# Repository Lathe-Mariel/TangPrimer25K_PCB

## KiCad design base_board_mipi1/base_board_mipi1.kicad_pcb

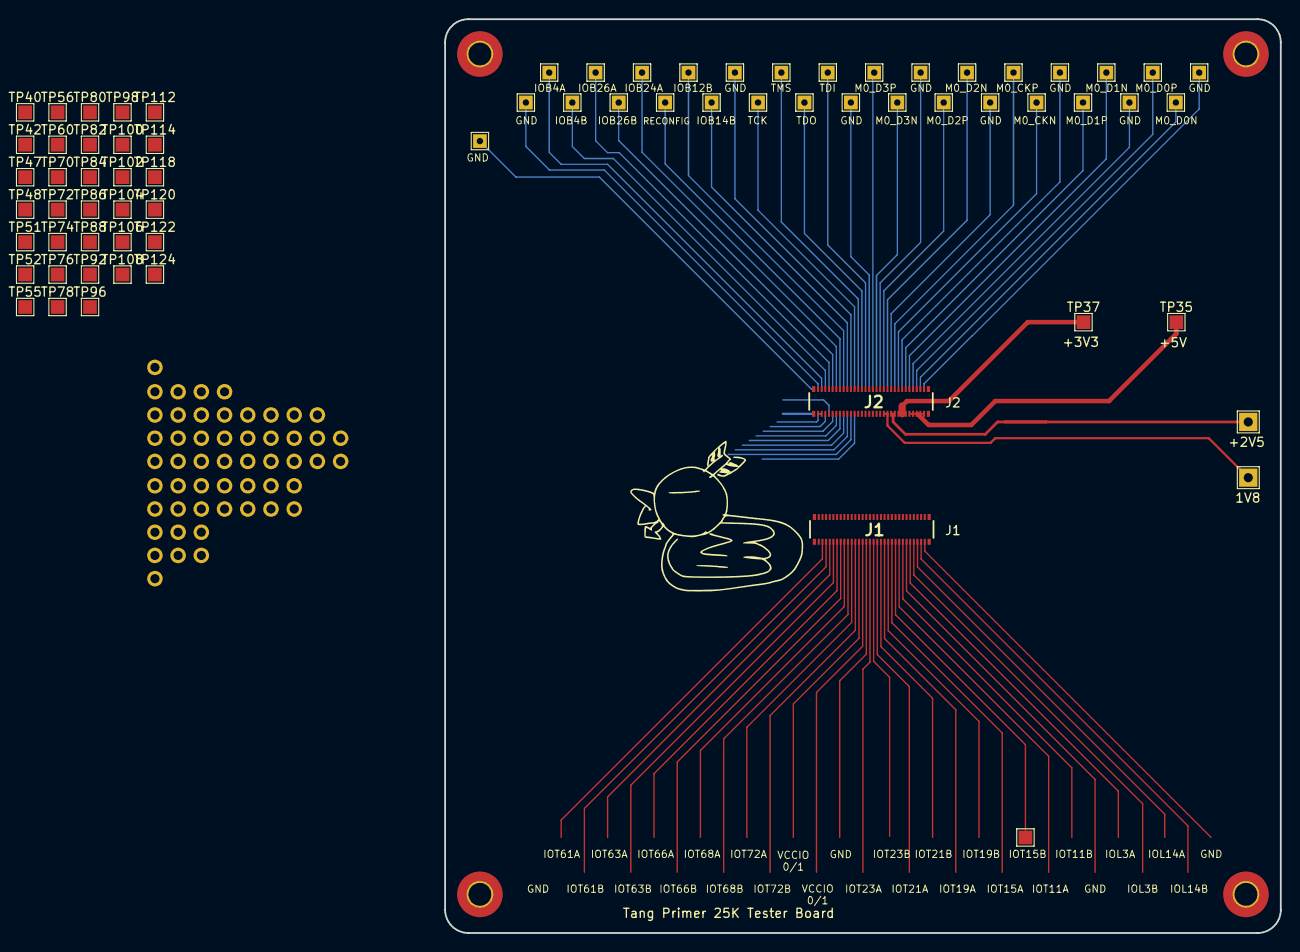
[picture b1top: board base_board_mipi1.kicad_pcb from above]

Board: 2 copper layers, 91.4 x 100.0 mm, 69 parts (0 on the bottom side), 55 nets.

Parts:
J1, J2: DF40C-60DP-0.4V_51_; DF40C-60DS-0.4V_51_
TP1, TP2, TP3, TP4, TP5, TP6, TP7, TP8, TP9, TP10, TP11, TP12, TP13, TP14, TP15, TP16, TP17, TP18, TP19, TP20, TP21, TP22, TP23, TP24, TP25, TP26, TP27, TP28, TP29, TP30, TP61: TestPoint; TestPoint_THTPad_1.5x1.5mm_Drill0.7mm
TP35, TP37, TP40, TP42, TP47, TP48, TP51, TP52, TP55, TP56, TP60, TP70, TP72, TP74, TP76, TP78, TP80, TP82, TP84, TP86, TP88, TP92, TP96, TP98, TP100, TP102, TP104, TP106, TP108, TP110, TP112, TP114, TP118, TP120, TP122, TP124: TestPoint; TestPoint_Pad_1.5x1.5mm

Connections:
+2V5: J2.42, J2.44, TP40.1
+3V3: J2.46, J2.48, J2.50, TP37.1
+5V: J2.52, J2.54, J2.56, J2.58, J2.60, TP35.1
/IOB26A: J2.7, TP27.1
/IOB26B: J2.9, TP26.1
/IOL3A: J1.52, TP118.1
/IOL3B: J1.54, TP120.1
/IOL14A: J1.56, TP122.1
/IOL14B: J1.58, TP124.1
/IOR20A: J2.10, TP56.1
/IOR20B: J2.12, TP55.1
/IOR24A: J2.18, TP52.1
/IOR24B: J2.20, TP51.1
/IOR33A: J2.26, TP48.1
/IOR33B: J2.28, TP47.1
/IOT11A: J1.46, TP112.1
/IOT11B: J1.48, TP114.1
/IOT15A: J1.42, TP108.1
/IOT15B: J1.44, TP110.1
/IOT19A: J1.38, TP104.1
/IOT19B: J1.40, TP106.1
/IOT21A: J1.34, TP100.1
/IOT21B: J1.36, TP102.1
/IOT23A: J1.30, TP96.1
/IOT23B: J1.32, TP98.1
/IOT61A: J1.4, TP70.1
/IOT61B: J1.6, TP72.1
/IOT63A: J1.8, TP74.1
/IOT63B: J1.10, TP76.1
/IOT66A: J1.12, TP78.1
/IOT66B: J1.14, TP80.1
/IOT68A: J1.16, TP82.1
/IOT68B: J1.18, TP84.1
/IOT72A: J1.20, TP86.1
/IOT72B: J1.22, TP88.1
/M0_CKN: J2.45, TP8.1
/M0_CKP: J2.43, TP9.1
/M0_D0N: J2.57, TP2.1
/M0_D0P: J2.55, TP3.1
/M0_D1N: J2.51, TP5.1
/M0_D1P: J2.49, TP6.1
/M0_D2N: J2.39, TP11.1
/M0_D2P: J2.37, TP12.1
/M0_D3N: J2.33, TP14.1
/M0_D3P: J2.31, TP15.1
/RECONFIG: J2.13, TP24.1
/TCK: J2.21, TP20.1
/TDI: J2.27, TP17.1
/TDO: J2.25, TP18.1
/TMS: J2.23, TP19.1
/VCCIO0/1: J1.24, J1.26, TP92.1
/VCCIO2/3: J2.2, J2.4, TP60.1
/VCCIO6/7: J1.29, J1.31
/VDD_1V8: J2.38, J2.40, TP42.1
GND: J1.1, J1.2, J1.15, J1.27, J1.28, J1.45, J1.50, J1.59, J1.60, J1.61, J1.62, J1.63, J1.64, J2.1, J2.19, J2.29, J2.35, J2.41, J2.47, J2.53, J2.59, J2.61, J2.62, J2.63, J2.64, TP1.1, TP4.1, TP7.1, TP10.1, TP13.1, TP16.1, TP21.1, TP30.1, TP61.1

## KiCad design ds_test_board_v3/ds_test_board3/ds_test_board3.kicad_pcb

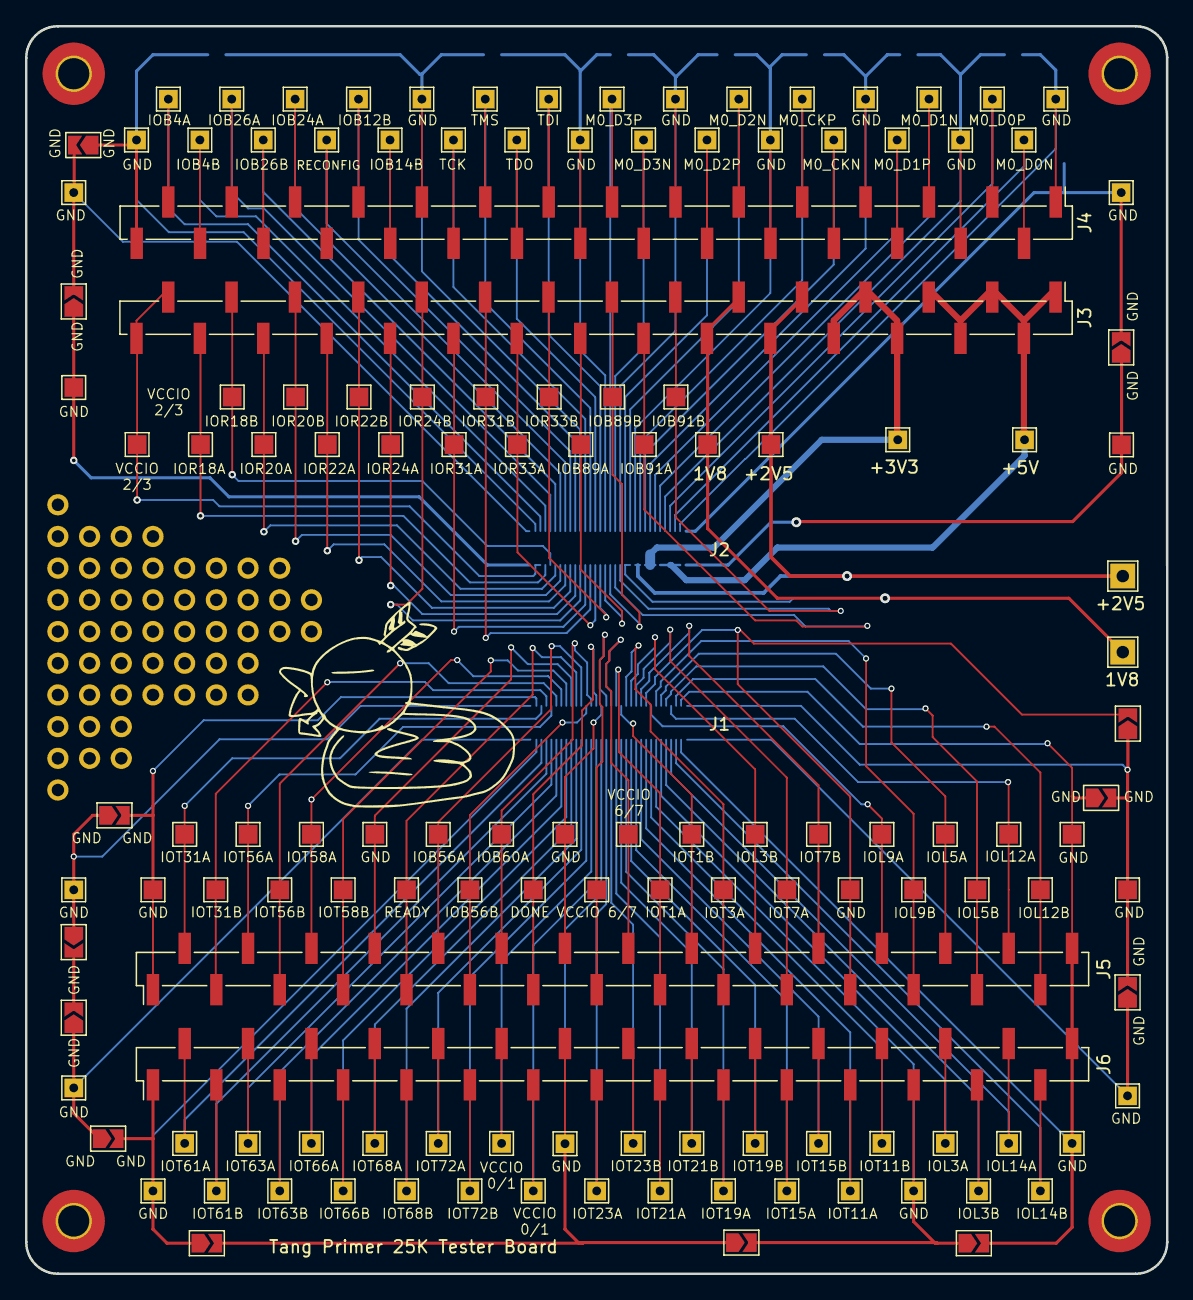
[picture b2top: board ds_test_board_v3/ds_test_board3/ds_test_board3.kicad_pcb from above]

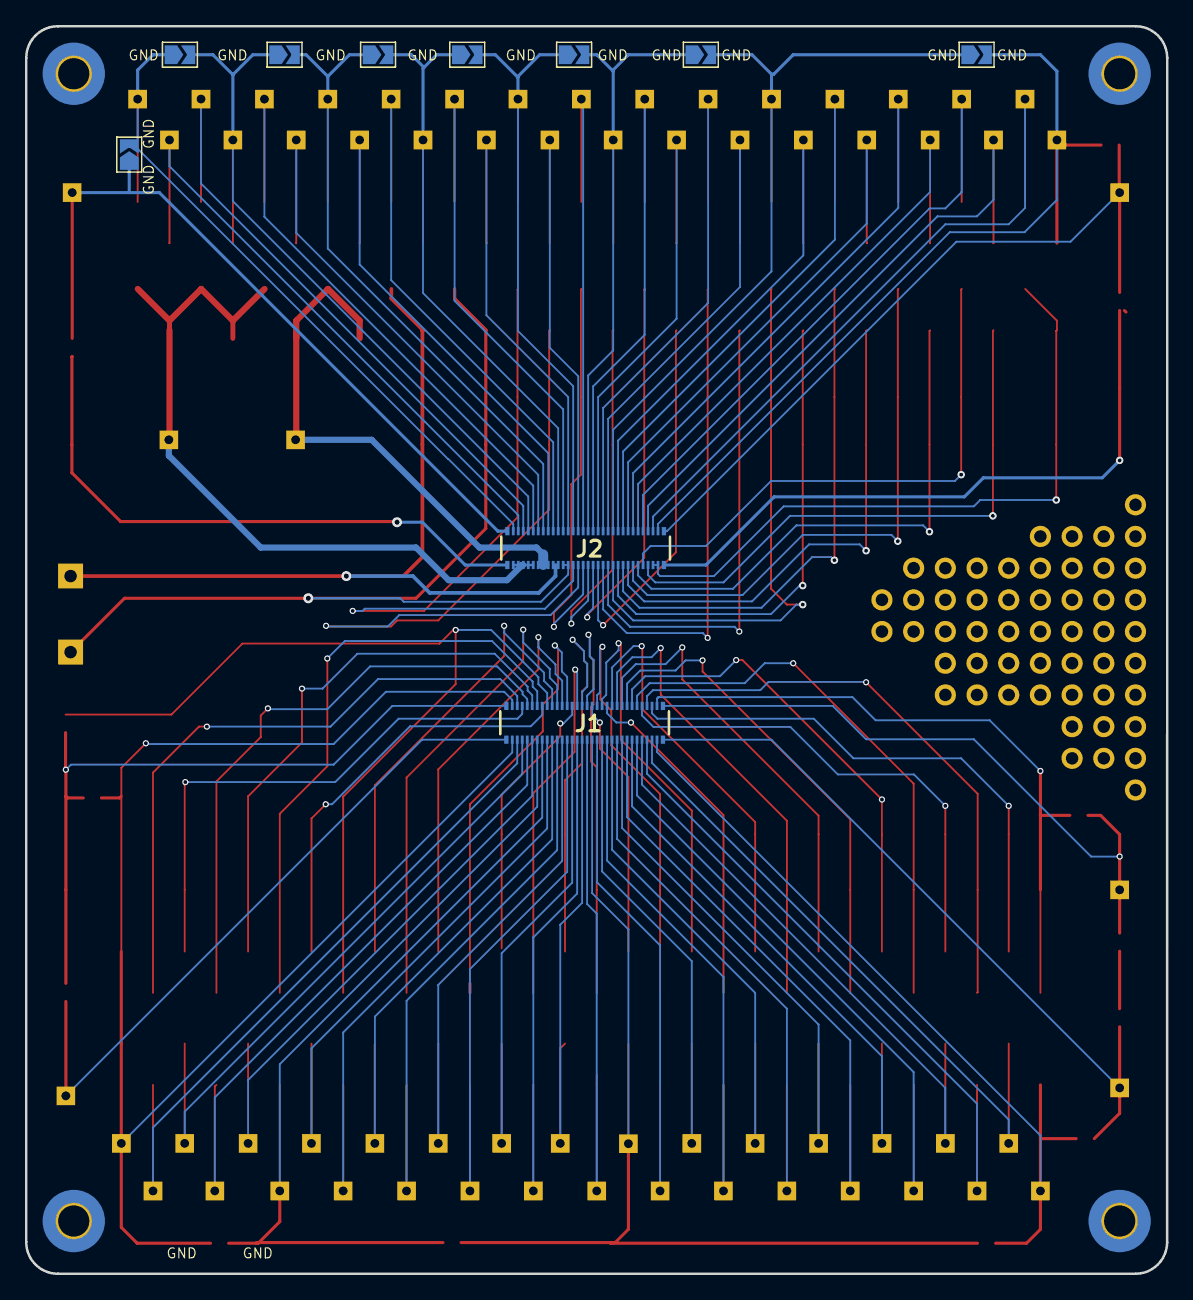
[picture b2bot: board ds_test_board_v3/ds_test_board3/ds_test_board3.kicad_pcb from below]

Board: 2 copper layers, 91.4 x 100.0 mm, 125 parts (2 on the bottom side), 97 nets.

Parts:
J1, J2: DF40C-60DP-0.4V_51_
J3, J4, J5, J6: Conn_01x30; PinHeader_1x30_P2.54mm_Vertical_SMD_Pin1Left
TP1, TP2, TP3, TP4, TP5, TP6, TP7, TP8, TP9, TP10, TP11, TP12, TP13, TP14, TP15, TP16, TP17, TP18, TP19, TP20, TP21, TP22, TP23, TP24, TP25, TP26, TP27, TP28, TP29, TP30, TP35, TP37, TP61, TP63, TP66, TP67, TP69, TP71, TP73, TP75, TP77, TP79, TP81, TP83, TP85, TP87, TP89, TP91, TP93, TP93#2, TP95, TP95#2, TP101, TP103, TP105, TP107, TP109, TP111, TP113, TP115, TP117, TP119, TP121, TP123, TP125, TP127, TP128: TestPoint; TestPoint_THTPad_1.5x1.5mm_Drill0.7mm
TP40, TP42, TP43, TP44, TP45, TP46, TP47, TP48, TP49, TP50, TP51, TP52, TP53, TP54, TP55, TP56, TP57, TP58, TP60, TP62, TP64, TP65, TP68, TP70, TP72, TP74, TP76, TP78, TP80, TP82, TP84, TP86, TP88, TP92, TP94, TP94#2, TP96, TP98, TP100, TP102, TP104, TP106, TP108, TP110, TP112, TP114, TP116, TP118, TP120, TP122, TP124, TP126: TestPoint; TestPoint_Pad_1.5x1.5mm

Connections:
+2V5: J2.42, J2.44, J3.9, J3.10, TP40.1
+3V3: J2.46, J2.48, J2.50, J3.6, J3.7, J3.8, TP37.1
+5V: J2.52, J2.54, J2.56, J2.58, J2.60, J3.1, J3.2, J3.3, J3.4, J3.5, TP35.1
/DONE: J1.25, J5.13, TP102.1
/IOB4A: J2.3, J4.29, TP29.1
/IOB4B: J2.5, J4.28, TP28.1
/IOB12B: J2.15, J4.23, TP23.1
/IOB14B: J2.17, J4.22, TP22.1
/IOB24A: J2.11, J4.25, TP25.1
/IOB26A: J2.7, J4.27, TP27.1
/IOB26B: J2.9, J4.26, TP26.1
/IOB56A: J1.19, J5.10, TP108.1
/IOB56B: J1.21, J5.11, TP106.1
/IOB60A: J1.23, J5.12, TP104.1
/IOB89A: J2.30, J3.16, TP46.1
/IOB89B: J2.32, J3.15, TP45.1
/IOB91A: J2.34, J3.14, TP44.1
/IOB91B: J2.36, J3.13, TP43.1
/IOL3A: J1.52, J6.26, TP75.1
/IOL3B: J1.54, J6.27, TP73.1
/IOL5A: J1.51, J5.26, TP76.1
/IOL5B: J1.53, J5.27, TP74.1
/IOL9A: J1.47, J5.24, TP80.1
/IOL9B: J1.49, J5.25, TP78.1
/IOL12A: J1.55, J5.28, TP72.1
/IOL12B: J1.57, J5.29, TP70.1
/IOL14A: J1.56, J6.28, TP71.1
/IOL14B: J1.58, J6.29, TP69.1
/IOR18A: J2.6, J3.28, TP58.1
/IOR18B: J2.8, J3.27, TP57.1
/IOR20A: J2.10, J3.26, TP56.1
/IOR20B: J2.12, J3.25, TP55.1
/IOR22A: J2.14, J3.24, TP54.1
/IOR22B: J2.16, J3.23, TP53.1
/IOR24A: J2.18, J3.22, TP52.1
/IOR24B: J2.20, J3.21, TP51.1
/IOR31A: J2.22, J3.20, TP50.1
/IOR31B: J2.24, J3.19, TP49.1
/IOR33A: J2.26, J3.18, TP48.1
/IOR33B: J2.28, J3.17, TP47.1
/IOT1A: J1.33, J5.17, TP94#2.1
/IOT1B: J1.35, J5.18, TP94.1
/IOT3A: J1.37, J5.19, TP92.1
/IOT3B: J1.39, J5.20, TP88.1
/IOT7A: J1.41, J5.21, TP86.1
/IOT7B: J1.43, J5.22, TP84.1
/IOT11A: J1.46, J6.23, TP81.1
/IOT11B: J1.48, J6.24, TP79.1
/IOT15A: J1.42, J6.21, TP85.1
/IOT15B: J1.44, J6.22, TP83.1
/IOT19A: J1.38, J6.19, TP89.1
/IOT19B: J1.40, J6.20, TP87.1
/IOT21A: J1.34, J6.17, TP93.1
/IOT21B: J1.36, J6.18, TP91.1
/IOT23A: J1.30, J6.15, TP95.1
/IOT23B: J1.32, J6.16, TP93#2.1
/IOT58A: J1.11, J5.6, TP116.1
/IOT58B: J1.13, J5.7, TP114.1
/IOT61A: J1.4, J6.2, TP123.1
/IOT61B: J1.6, J6.3, TP121.1
/IOT63A: J1.8, J6.4, TP119.1
/IOT63B: J1.10, J6.5, TP117.1
/IOT66A: J1.12, J6.6, TP115.1
/IOT66B: J1.14, J6.7, TP113.1
/IOT68A: J1.16, J6.8, TP111.1
/IOT68B: J1.18, J6.9, TP109.1
/IOT72A: J1.20, J6.10, TP107.1
/IOT72B: J1.22, J6.11, TP105.1
/M0_CKN: J2.45, J4.8, TP8.1
/M0_CKP: J2.43, J4.9, TP9.1
/M0_D0N: J2.57, J4.2, TP2.1
/M0_D0P: J2.55, J4.3, TP3.1
/M0_D1N: J2.51, J4.5, TP5.1
/M0_D1P: J2.49, J4.6, TP6.1
/M0_D2N: J2.39, J4.11, TP11.1
/M0_D2P: J2.37, J4.12, TP12.1
/M0_D3N: J2.33, J4.14, TP14.1
/M0_D3P: J2.31, J4.15, TP15.1
/READY: J1.17, J5.9, TP110.1
/RECONFIG: J2.13, J4.24, TP24.1
/TCK: J2.21, J4.20, TP20.1
/TDI: J2.27, J4.17, TP17.1
/TDO: J2.25, J4.18, TP18.1
/TMS: J2.23, J4.19, TP19.1
/VCCIO0/1: J1.24, J1.26, J6.12, J6.13, TP101.1, TP103.1
/VCCIO2/3: J2.2, J2.4, J3.29, J3.30, TP60.1
/VCCIO6/7: J1.29, J1.31, J5.15, J5.16, TP96.1, TP98.1
/VDD_1V8: J2.38, J2.40, J3.11, J3.12, TP42.1
GND: J1.1, J1.2, J1.15, J1.27, J1.28, J1.45, J1.50, J1.59, J1.60, J2.1, J2.19, J2.29, J2.35, J2.41, J2.47, J2.53, J2.59, J2.61, J2.62, J2.63, J2.64, J4.1, J4.4, J4.7, J4.10, J4.13, J4.16, J4.21, J4.30, J5.1, J5.8, J5.14, J5.23, J5.30, J6.1, J6.14, J6.25, J6.30, TP1.1, TP4.1, TP7.1, TP10.1, TP13.1, TP16.1, TP21.1, TP30.1, TP61.1, TP62.1, TP63.1, TP64.1, TP67.1, TP68.1, TP77.1, TP82.1, TP95#2.1, TP100.1, TP112.1, TP125.1, TP126.1
IOT31A: J1.3, J5.2, TP124.1
IOT31B: J1.5, J5.3, TP122.1
IOT56A: J1.7, J5.4, TP120.1
IOT56B: J1.9, J5.5, TP118.1
unnamed: J1.61, TP128.1
unnamed: J1.62, TP127.1
unnamed: J1.63, TP65.1
unnamed: J1.64, TP66.1

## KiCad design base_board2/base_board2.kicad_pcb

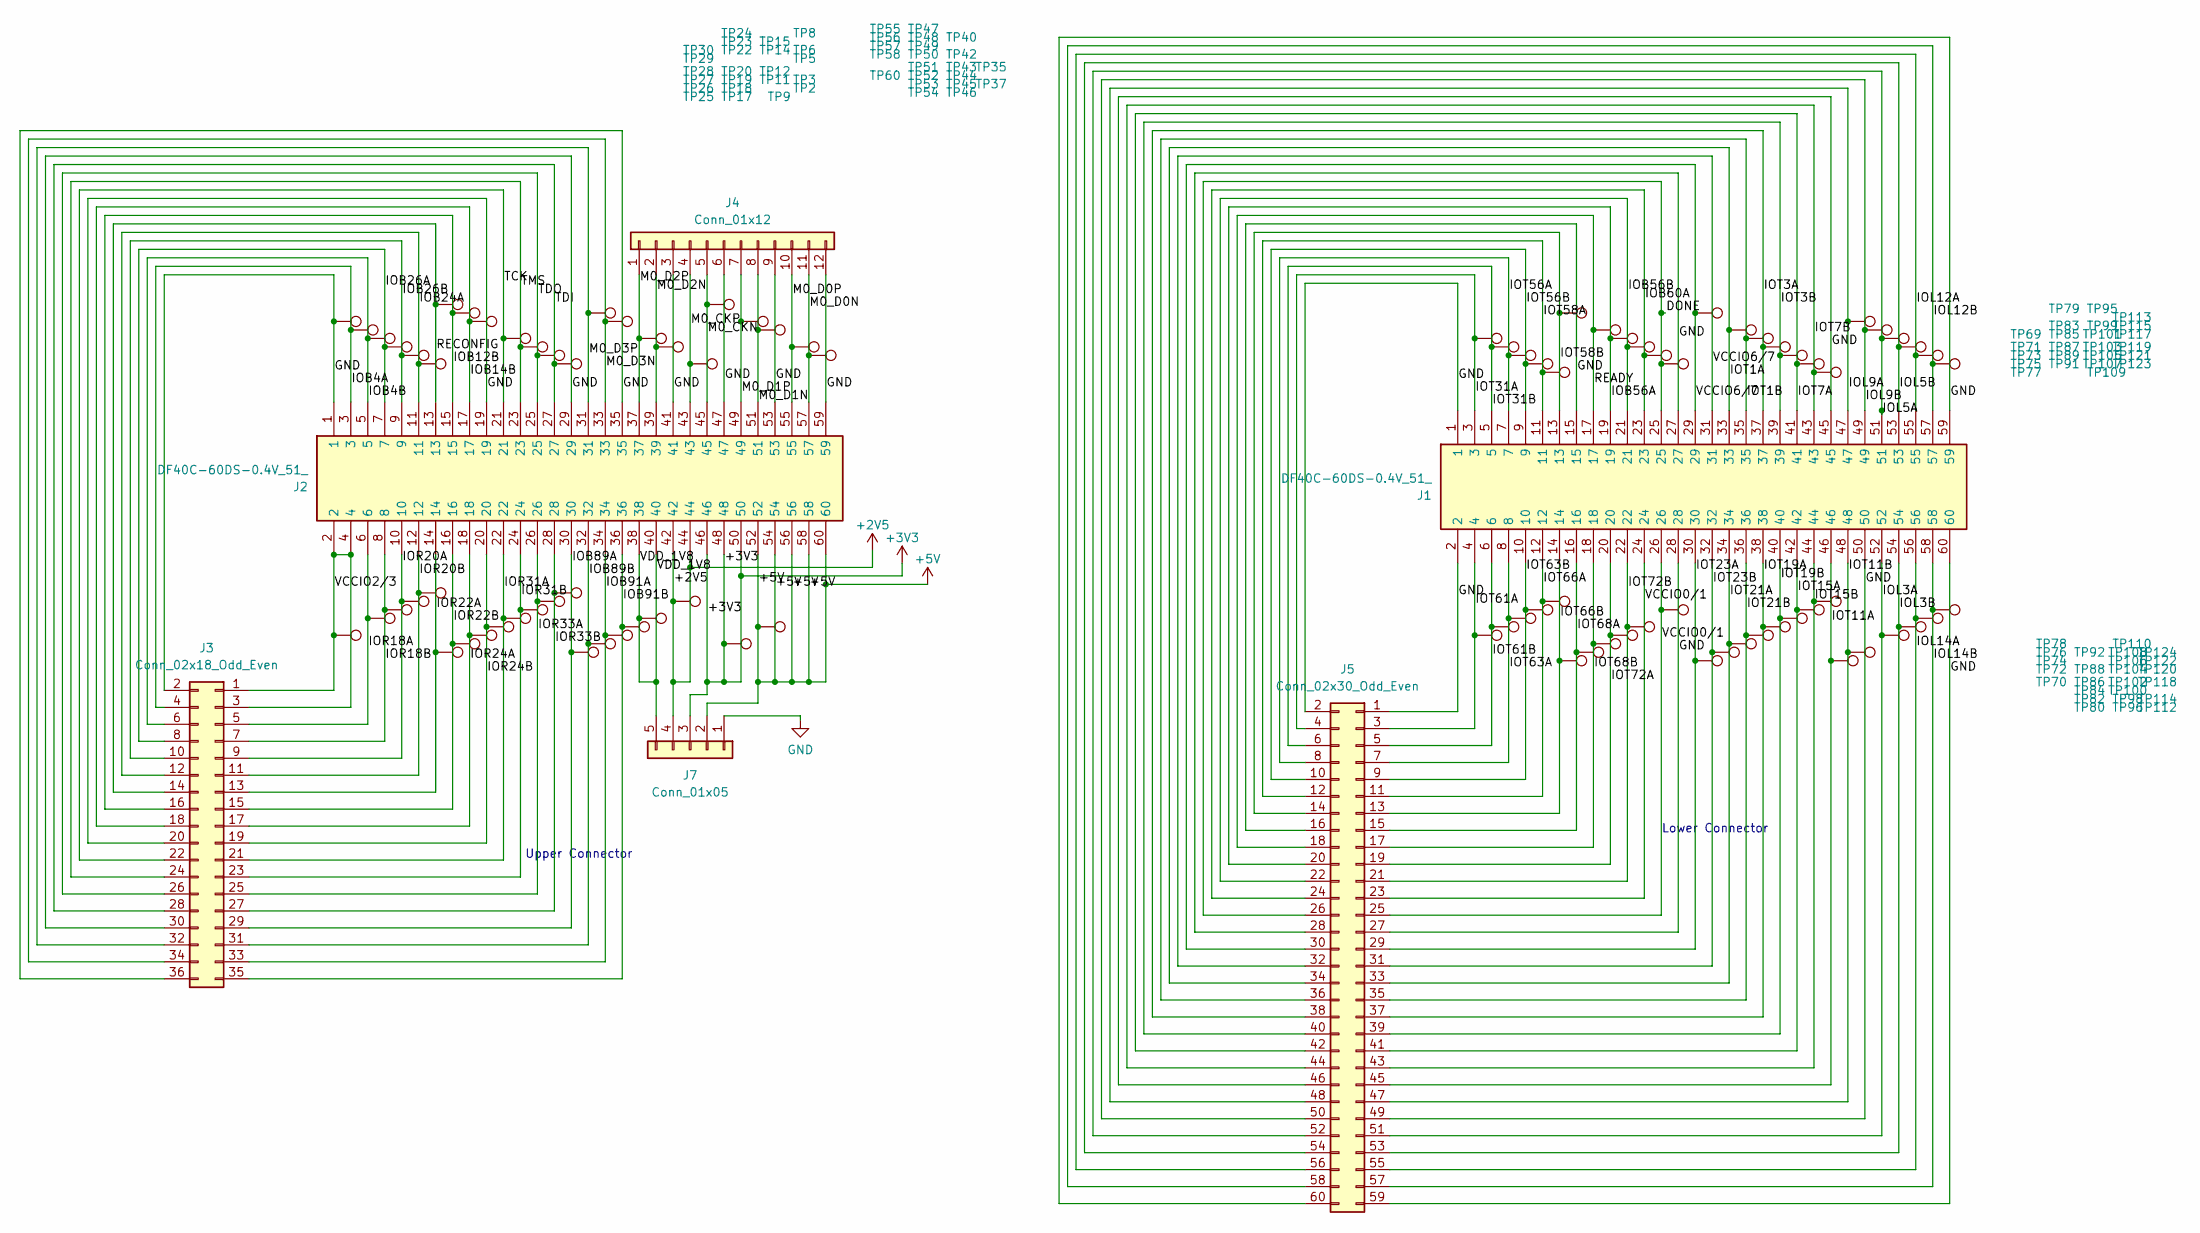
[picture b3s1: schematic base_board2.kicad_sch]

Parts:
J1, J2: DF40C-60DS-0.4V_51_; DF40C60DS04V51; Manufacturer_Part_Number DF40C-60DS-0.4V(51)
J3: Conn_02x18_Odd_Even; PinSocket_2x18_P2.54mm_Vertical
J4: Conn_01x12; PinSocket_1x12_P2.54mm_Vertical
J5: Conn_02x30_Odd_Even; PinSocket_2x30_P2.54mm_Vertical
J7: Conn_01x05; PinSocket_1x05_P2.54mm_Vertical
TP2, TP3, TP5, TP6, TP8, TP9, TP11, TP12, TP14, TP15, TP17, TP18, TP19, TP20, TP22, TP23, TP24, TP25, TP26, TP27, TP28, TP29, TP30, TP70, TP72, TP74, TP76, TP78, TP80, TP82, TP84, TP86, TP88, TP92, TP96, TP98, TP100, TP102, TP104, TP106, TP108, TP110, TP112, TP114, TP118, TP120, TP122, TP124: TestPoint; TestPoint_Pad_1.5x1.5mm
TP35, TP37, TP40, TP42, TP43, TP44, TP45, TP46, TP47, TP48, TP49, TP50, TP51, TP52, TP53, TP54, TP55, TP56, TP57, TP58, TP60, TP69, TP71, TP73, TP75, TP77, TP79, TP83, TP85, TP87, TP89, TP91, TP95, TP99, TP101, TP103, TP105, TP107, TP109, TP113, TP115, TP117, TP119, TP121, TP123: TestPoint; TestPoint_THTPad_1.5x1.5mm_Drill0.7mm

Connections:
+2V5: J2.42, J2.44, J7.4, TP40.1
+3V3: J2.46, J2.48, J2.50, J7.3, TP37.1
+5V: J2.52, J2.54, J2.56, J2.58, J2.60, J7.2, TP35.1
/DONE: J1.25, J5.26, TP91.1
/IOB4A: J2.3, J3.4, TP29.1
/IOB4B: J2.5, J3.6, TP28.1
/IOB12B: J2.15, J3.16, TP23.1
/IOB14B: J2.17, J3.18, TP22.1
/IOB24A: J2.11, J3.12, TP25.1
/IOB26A: J2.7, J3.8, TP27.1
/IOB26B: J2.9, J3.10, TP26.1
/IOB56A: J1.19, J5.20, TP85.1
/IOB56B: J1.21, J5.22, TP87.1
/IOB60A: J1.23, J5.24, TP89.1
/IOB89A: J2.30, J3.29, TP46.1
/IOB89B: J2.32, J3.31, TP45.1
/IOB91A: J2.34, J3.33, TP44.1
/IOB91B: J2.36, J3.35, TP43.1
/IOL3A: J1.52, J5.51, TP118.1
/IOL3B: J1.54, J5.53, TP120.1
/IOL5A: J1.51, J5.52, TP117.1
/IOL5B: J1.53, J5.54, TP119.1
/IOL9A: J1.47, J5.48, TP113.1
/IOL9B: J1.49, J5.50, TP115.1
/IOL12A: J1.55, J5.56, TP121.1
/IOL12B: J1.57, J5.58, TP123.1
/IOL14A: J1.56, J5.55, TP122.1
/IOL14B: J1.58, J5.57, TP124.1
/IOR18A: J2.6, J3.5, TP58.1
/IOR18B: J2.8, J3.7, TP57.1
/IOR20A: J2.10, J3.9, TP56.1
/IOR20B: J2.12, J3.11, TP55.1
/IOR22A: J2.14, J3.13, TP54.1
/IOR22B: J2.16, J3.15, TP53.1
/IOR24A: J2.18, J3.17, TP52.1
/IOR24B: J2.20, J3.19, TP51.1
/IOR31A: J2.22, J3.21, TP50.1
/IOR31B: J2.24, J3.23, TP49.1
/IOR33A: J2.26, J3.25, TP48.1
/IOR33B: J2.28, J3.27, TP47.1
/IOT1A: J1.33, J5.34, TP99.1
/IOT1B: J1.35, J5.36, TP101.1
/IOT3A: J1.37, J5.38, TP103.1
/IOT3B: J1.39, J5.40, TP105.1
/IOT7A: J1.41, J5.42, TP107.1
/IOT7B: J1.43, J5.44, TP109.1
/IOT11A: J1.46, J5.45, TP112.1
/IOT11B: J1.48, J5.47, TP114.1
/IOT15A: J1.42, J5.41, TP108.1
/IOT15B: J1.44, J5.43, TP110.1
/IOT19A: J1.38, J5.37, TP104.1
/IOT19B: J1.40, J5.39, TP106.1
/IOT21A: J1.34, J5.33, TP100.1
/IOT21B: J1.36, J5.35, TP102.1
/IOT23A: J1.30, J5.29, TP96.1
/IOT23B: J1.32, J5.31, TP98.1
/IOT31A: J1.3, J5.4, TP69.1
/IOT31B: J1.5, J5.6, TP71.1
/IOT56A: J1.7, J5.8, TP73.1
/IOT56B: J1.9, J5.10, TP75.1
/IOT58A: J1.11, J5.12, TP77.1
/IOT58B: J1.13, J5.14, TP79.1
/IOT61A: J1.4, J5.3, TP70.1
/IOT61B: J1.6, J5.5, TP72.1
/IOT63A: J1.8, J5.7, TP74.1
/IOT63B: J1.10, J5.9, TP76.1
/IOT66A: J1.12, J5.11, TP78.1
/IOT66B: J1.14, J5.13, TP80.1
/IOT68A: J1.16, J5.15, TP82.1
/IOT68B: J1.18, J5.17, TP84.1
/IOT72A: J1.20, J5.19, TP86.1
/IOT72B: J1.22, J5.21, TP88.1
/M0_CKN: J2.45, J4.5, TP8.1
/M0_CKP: J2.43, J4.4, TP9.1
/M0_D0N: J2.57, J4.11, TP2.1
/M0_D0P: J2.55, J4.10, TP3.1
/M0_D1N: J2.51, J4.8, TP5.1
/M0_D1P: J2.49, J4.7, TP6.1
/M0_D2N: J2.39, J4.2, TP11.1
/M0_D2P: J2.37, J4.1, TP12.1
/M0_D3N: J2.33, J3.34, TP14.1
/M0_D3P: J2.31, J3.32, TP15.1
/READY: J1.17, J5.18, TP83.1
/RECONFIG: J2.13, J3.14, TP24.1
/TCK: J2.21, J3.22, TP20.1
/TDI: J2.27, J3.28, TP17.1
/TDO: J2.25, J3.26, TP18.1
/TMS: J2.23, J3.24, TP19.1
/VCCIO0/1: J1.24, J1.26, J5.23, J5.25, TP92.1
/VCCIO2/3: J2.2, J2.4, J3.1, J3.3, TP60.1
/VCCIO6/7: J1.29, J1.31, J5.30, J5.32, TP95.1
/VDD_1V8: J2.38, J2.40, J7.5, TP42.1
GND: J1.1, J1.2, J1.15, J1.27, J1.28, J1.45, J1.50, J1.59, J1.60, J2.1, J2.19, J2.29, J2.35, J2.41, J2.47, J2.53, J2.59, J3.2, J3.20, J3.30, J3.36, J4.3, J4.6, J4.9, J4.12, J5.1, J5.2, J5.16, J5.27, J5.28, J5.46, J5.49, J5.59, J5.60, J7.1, TP30.1; also elsewhere on the board

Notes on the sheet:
Lower Connector
Upper Connector

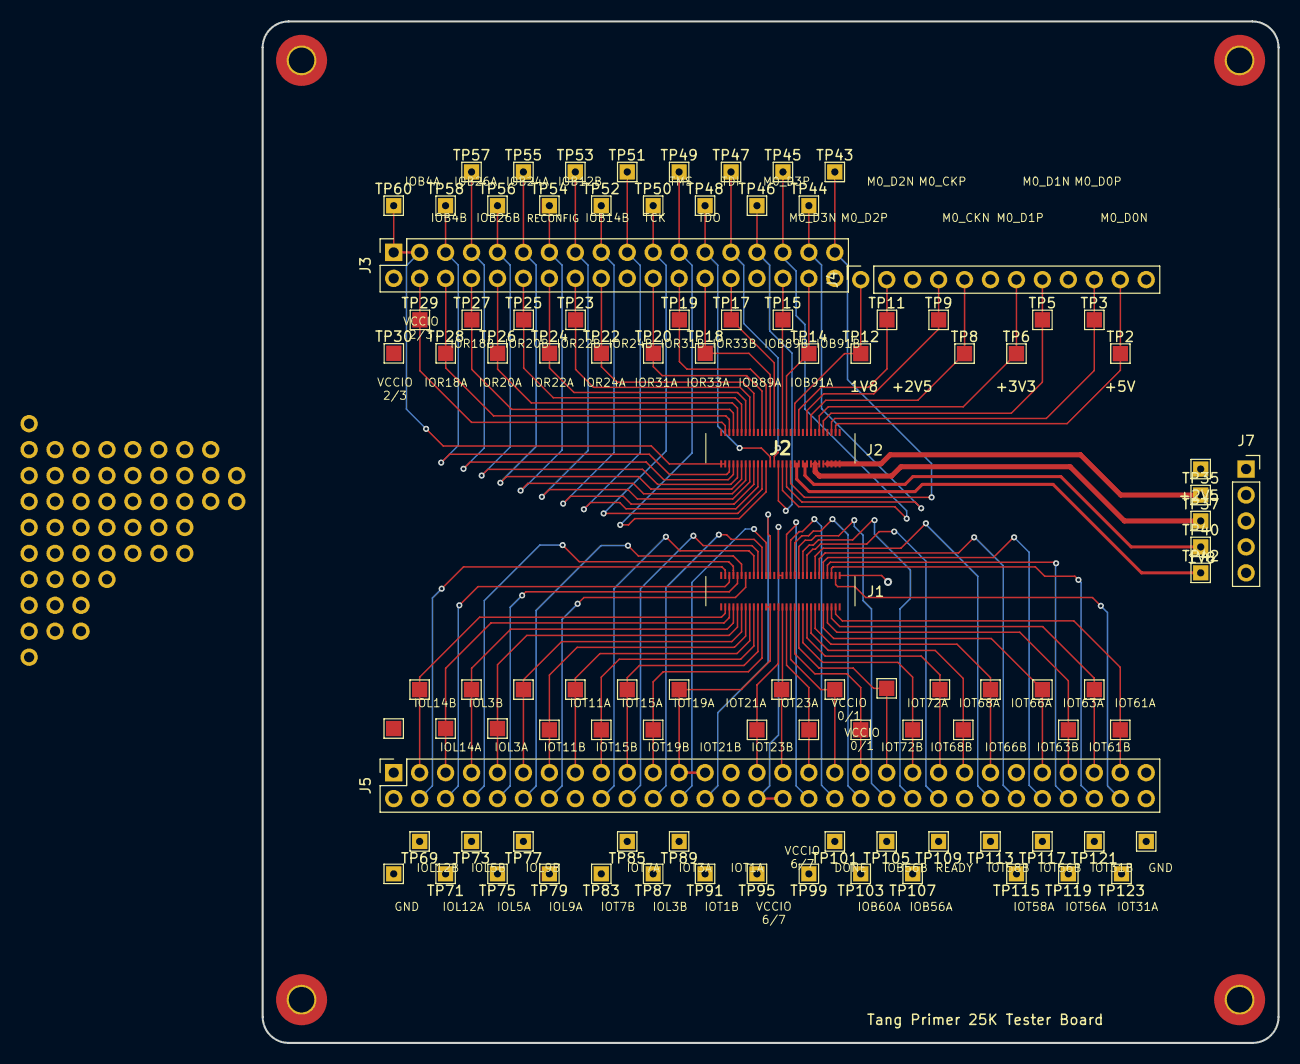
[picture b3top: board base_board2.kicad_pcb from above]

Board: 2 copper layers, 99.4 x 100.0 mm, 103 parts (0 on the bottom side), 93 nets.

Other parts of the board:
TP1, TP67, TP125: TestPoint; TestPoint_THTPad_1.5x1.5mm_Drill0.7mm
TP126: TestPoint; TestPoint_Pad_1.5x1.5mm

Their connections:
GND: TP1.1, TP67.1, TP125.1, TP126.1; also elsewhere on the board

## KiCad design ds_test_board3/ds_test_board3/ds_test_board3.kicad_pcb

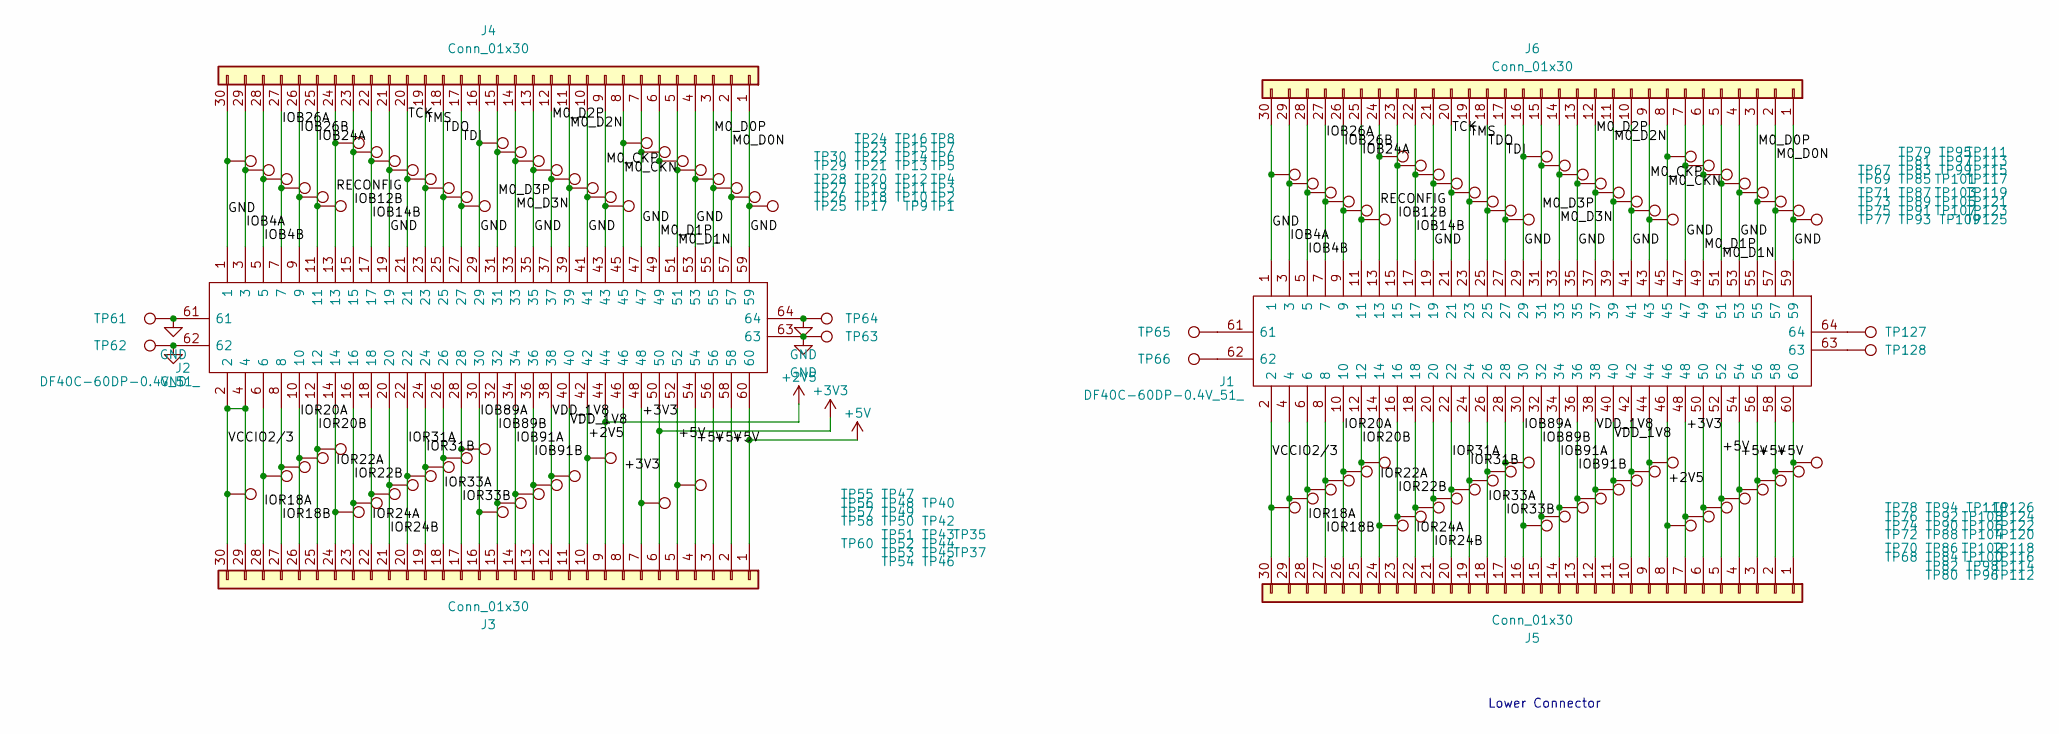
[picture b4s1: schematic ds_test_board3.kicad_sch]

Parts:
J1, J2: DF40C-60DP-0.4V_51_; Manufacturer_Part_Number DF40C-60DP-0.4V(51)
J3, J4, J5, J6: Conn_01x30; PinHeader_1x30_P2.54mm_Vertical_SMD_Pin1Left
TP1, TP2, TP3, TP4, TP5, TP6, TP7, TP8, TP9, TP10, TP11, TP12, TP13, TP14, TP15, TP16, TP17, TP18, TP19, TP20, TP21, TP22, TP23, TP24, TP25, TP26, TP27, TP28, TP29, TP30, TP61, TP63: TestPoint; TestPoint_THTPad_1.5x1.5mm_Drill0.7mm
TP35, TP37, TP40, TP42, TP43, TP44, TP45, TP46, TP47, TP48, TP49, TP50, TP51, TP52, TP53, TP54, TP55, TP56, TP57, TP58, TP60, TP62, TP64, TP65, TP66, TP67, TP68, TP69, TP70, TP71, TP72, TP73, TP74, TP75, TP76, TP77, TP78, TP79, TP80, TP81, TP82, TP83, TP84, TP85, TP86, TP87, TP88, TP89, TP90, TP91, TP92, TP93, TP94, TP95, TP96, TP97, TP98, TP99, TP100, TP101, TP102, TP103, TP104, TP105, TP106, TP107, TP108, TP109, TP110, TP111, TP112, TP113, TP114, TP115, TP116, TP117, TP118, TP119, TP120, TP121, TP122, TP123, TP124, TP125, TP126, TP127, TP128: TestPoint; TestPoint_Pad_1.5x1.5mm

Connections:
+2V5: J1.46, J2.42, J2.44, J3.9, J3.10, J5.8, TP40.1, TP112.1
+3V3: J1.48, J2.46, J2.48, J2.50, J3.6, J3.7, J3.8, J5.7, TP37.1, TP114.1
+5V: J1.52, J1.54, J1.56, J1.58, J2.52, J2.54, J2.56, J2.58, J2.60, J3.1, J3.2, J3.3, J3.4, J3.5, J5.2, J5.3, J5.4, J5.5, TP35.1, TP118.1, TP120.1, TP122.1, TP124.1
/IOB4A: J1.3, J2.3, J4.29, J6.29, TP29.1, TP69.1
/IOB4B: J1.5, J2.5, J4.28, J6.28, TP28.1, TP71.1
/IOB12B: J1.15, J2.15, J4.23, J6.23, TP23.1, TP81.1
/IOB14B: J1.17, J2.17, J4.22, J6.22, TP22.1, TP83.1
/IOB24A: J1.11, J2.11, J4.25, J6.25, TP25.1, TP77.1
/IOB26A: J1.7, J2.7, J4.27, J6.27, TP27.1, TP73.1
/IOB26B: J1.9, J2.9, J4.26, J6.26, TP26.1, TP75.1
/IOB89A: J1.30, J2.30, J3.16, J5.16, TP46.1, TP96.1
/IOB89B: J1.32, J2.32, J3.15, J5.15, TP45.1, TP98.1
/IOB91A: J1.34, J2.34, J3.14, J5.14, TP44.1, TP100.1
/IOB91B: J1.36, J2.36, J3.13, J5.13, TP43.1, TP102.1
/IOR18A: J1.6, J2.6, J3.28, J5.28, TP58.1, TP72.1
/IOR18B: J1.8, J2.8, J3.27, J5.27, TP57.1, TP74.1
/IOR20A: J1.10, J2.10, J3.26, J5.26, TP56.1, TP76.1
/IOR20B: J1.12, J2.12, J3.25, J5.25, TP55.1, TP78.1
/IOR22A: J1.14, J2.14, J3.24, J5.24, TP54.1, TP80.1
/IOR22B: J1.16, J2.16, J3.23, J5.23, TP53.1, TP82.1
/IOR24A: J1.18, J2.18, J3.22, J5.22, TP52.1, TP84.1
/IOR24B: J1.20, J2.20, J3.21, J5.21, TP51.1, TP86.1
/IOR31A: J1.22, J2.22, J3.20, J5.20, TP50.1, TP88.1
/IOR31B: J1.24, J2.24, J3.19, J5.19, TP49.1, TP90.1
/IOR33A: J1.26, J2.26, J3.18, J5.18, TP48.1, TP92.1
/IOR33B: J1.28, J2.28, J3.17, J5.17, TP47.1, TP94.1
/M0_CKN: J1.45, J2.45, J4.8, J6.8, TP8.1, TP111.1
/M0_CKP: J1.43, J2.43, J4.9, J6.9, TP9.1, TP109.1
/M0_D0N: J1.57, J2.57, J4.2, J6.2, TP2.1, TP123.1
/M0_D0P: J1.55, J2.55, J4.3, J6.3, TP3.1, TP121.1
/M0_D1N: J1.51, J2.51, J4.5, J6.5, TP5.1, TP117.1
/M0_D1P: J1.49, J2.49, J4.6, J6.6, TP6.1, TP115.1
/M0_D2N: J1.39, J2.39, J4.11, J6.11, TP11.1, TP105.1
/M0_D2P: J1.37, J2.37, J4.12, J6.12, TP12.1, TP103.1
/M0_D3N: J1.33, J2.33, J4.14, J6.14, TP14.1, TP99.1
/M0_D3P: J1.31, J2.31, J4.15, J6.15, TP15.1, TP97.1
/RECONFIG: J1.13, J2.13, J4.24, J6.24, TP24.1, TP79.1
/TCK: J1.21, J2.21, J4.20, J6.20, TP20.1, TP87.1
/TDI: J1.27, J2.27, J4.17, J6.17, TP17.1, TP93.1
/TDO: J1.25, J2.25, J4.18, J6.18, TP18.1, TP91.1
/TMS: J1.23, J2.23, J4.19, J6.19, TP19.1, TP89.1
/VCCIO2/3: J1.2, J2.2, J2.4, J3.29, J3.30, J5.30, TP60.1, TP68.1
/VDD_1V8: J1.38, J1.40, J2.38, J2.40, J3.11, J3.12, J5.11, J5.12, TP42.1, TP104.1, TP106.1
GND: J1.1, J1.19, J1.29, J1.35, J1.41, J1.47, J1.53, J1.59, J2.1, J2.19, J2.29, J2.35, J2.41, J2.47, J2.53, J2.59, J2.61, J2.62, J2.63, J2.64, J4.1, J4.4, J4.7, J4.10, J4.13, J4.16, J4.21, J4.30, J6.1, J6.4, J6.7, J6.10, J6.13, J6.16, J6.21, J6.30, TP1.1, TP4.1, TP7.1, TP10.1, TP13.1, TP16.1, TP21.1, TP30.1, TP61.1, TP62.1, TP63.1, TP64.1, TP67.1, TP85.1, TP95.1, TP101.1, TP107.1, TP113.1, TP119.1, TP125.1
unnamed: J1.61, TP65.1
unnamed: J1.62, TP66.1
unnamed: J1.63, TP128.1
unnamed: J1.64, TP127.1
unnamed: J1.60, J5.1, TP126.1
unnamed: J1.50, J5.6, TP116.1
unnamed: J1.44, J5.9, TP110.1
unnamed: J1.42, J5.10, TP108.1
unnamed: J1.4, J5.29, TP70.1

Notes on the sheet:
Lower Connector

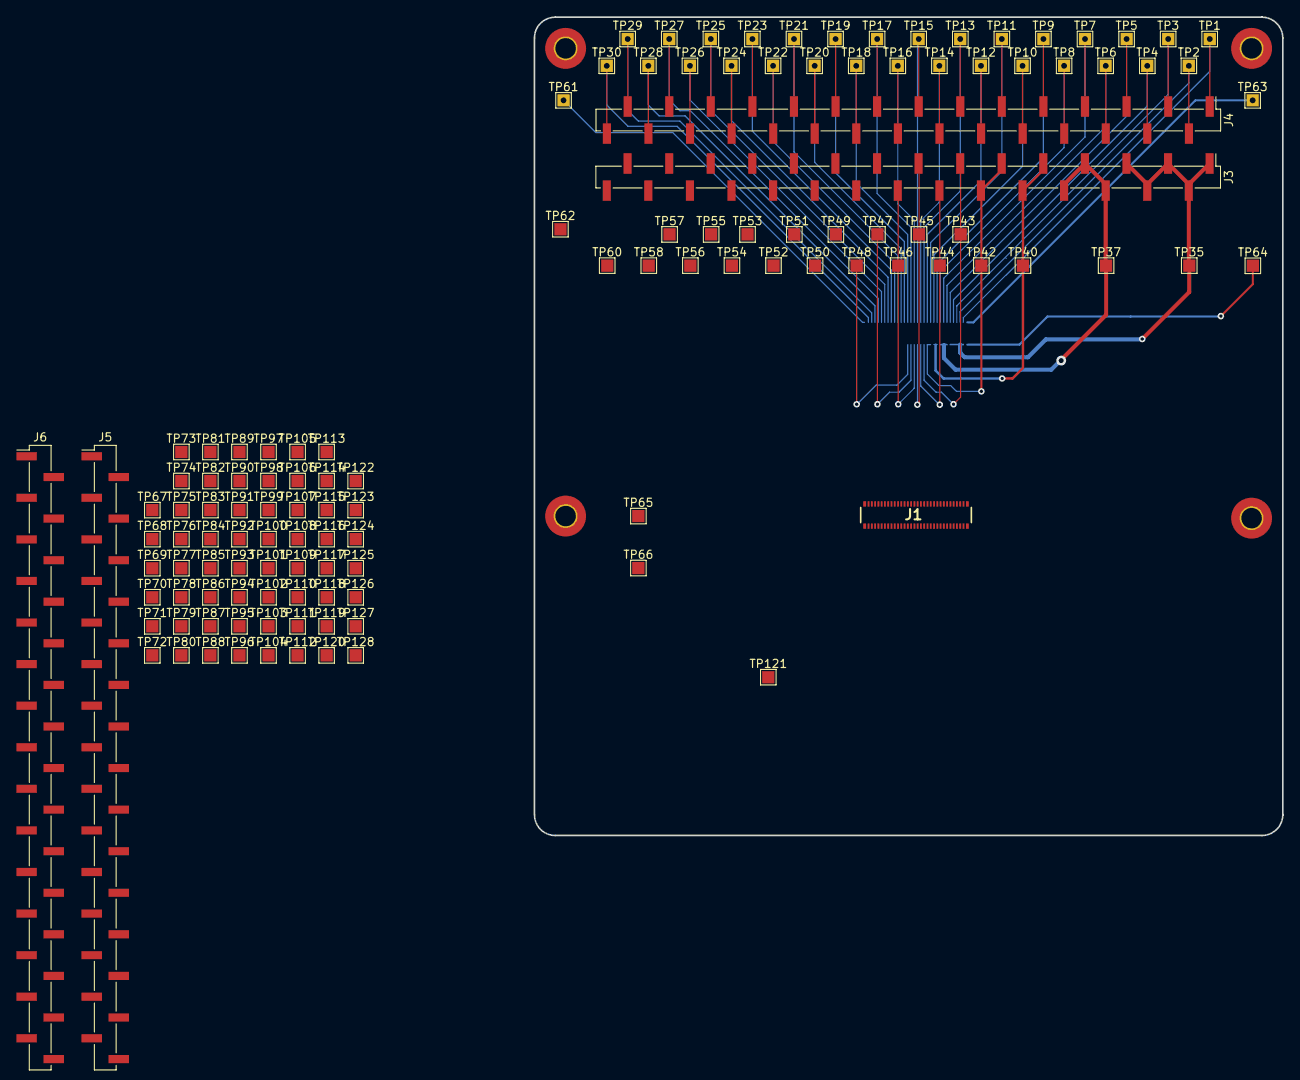
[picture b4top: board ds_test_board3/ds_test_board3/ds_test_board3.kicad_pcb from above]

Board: 2 copper layers, 91.4 x 100.0 mm, 125 parts (1 on the bottom side), 53 nets.
